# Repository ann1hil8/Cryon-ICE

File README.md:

# Cryon-ICE: High-Performance RISC-V Target Emulator & Hardware Debugger

Cryon-ICE is a high-speed real-time hardware debugger and target emulation platform built on the Microchip PolarFire SoC FPGA architecture. The system serves as an advanced bidirectional interface bridge designed to intercept, analyze, and process target system execution signals with sub-nanosecond timing precision. 

The architecture bridges a multi-core 64-bit Linux-capable RISC-V subsystem and flexible programmable fabric directly to an external emulation pod interface via high-density card edge connectors.

---

## Technical Architecture Overview

### 1. System Function & Target Application
* **Real-Time Emulation:** Provides deterministic, ultra-low-latency tracking and signal injection for vintage and modern processing buses.
* **Signal Intercept:** Actively hooks into address, data, and control structures of external hardware targets through dedicated, direction-controlled level shifters.
* **Bus Topologies:** Supports a universal expansion bus configuration, currently mapped to a physical PCIe card edge connector profile to interface directly with modular target emulation pods.

### 2. Primary Processing Core
The platform core utilizes the **Microchip PolarFire SoC FPGA** which integrates a hardened coherent CPU cluster alongside non-volatile programmable logic fabric.

* **Exact Part Number:** `MPFS025TC-FCVG484I` (Industrial Temperature Variant, 25K Logic Elements).
* **Microprocessor Sub-System (MSS):** * 1x RV64IMAC Monitor Core (E51 Performance Profile).
  * 4x RV64GC Application Cores (U54 Performance Profile, coherent execution cluster).
  * Hardened memory controllers supporting secure boot, asset protection, and full operating system execution (Linux).
* **Reference Baselines:** Hardware schematics and subsystem initialization fabrics are cross-referenced from the **BeagleV-Fire** open-hardware specification and the **MPFS-ICICLE-KIT** (PolarFire SoC Icicle Development Kit) base architectures.

### 3. Physical Mechanical Package
* **Package Designation:** `FCVG484` (Fine Pitch Flip-Chip Ball Grid Array).
* **Physical Package Envelope:** 19.0 mm x 19.0 mm square molded body package size.
* **Pin Matrix Array:** 484 physical active solder spheres mapped to a 22 x 22 structural matrix grid.
* **Ball Pitch ($P$):** 0.8 mm center-to-center pad spacing. This allows routing single escape tracks using conventional, cost-effective mechanical micro-drills rather than high-density interconnect (HDI) laser-vias.

### 4. PCB Design & Layout Constraints

#### Thermal and Decoupling Void
The physical layout strips away all copper landing pads within the center core of the 22 x 22 BGA matrix configuration, mirroring the physical depopulated ring profile of the `FCVG484` package silicon. This provides two critical routing advantages:
* **Decoupling Optimization:** Low-inductance 0.1 uF ceramic decoupling capacitors are placed directly on the bottom side of the PCB (Layer 4/6), directly beneath the processor power balls to suppress high-frequency transients.
* **Thermal Sink:** The internal center cavity is flooded with a continuous, unbroken Ground copper polygon pour on the outer layer, functioning as an integrated cooling block connected directly to internal system return layers.

#### Physical Layer Stackup Blueprint
The system requires a minimum of a 4-Layer or 6-Layer impedance-controlled configuration:
* **Layer 1 (Top/F.Cu):** Microstrip routing paths, BGA outer escape rings, high-speed transceiver runs, and level-shifter landing pads.
* **Layer 2 (Inner 1/In1.Cu):** Continuous, uninterrupted Ground ($GND$) reference plane. Provides immediate shield parameters for high-density breakout tracks.
* **Layer 3 (Inner 2/In2.Cu):** Split Power Plane ($V_{\text{DD}}$ Core Logic, $V_{\text{DDA}}$ Transceiver Supplies, and 3.3 V / 5.0 V I/O Peripheral Rails).
* **Layer 4 (Bottom/B.Cu):** Passives, decoupling capacitors under the BGA core cavity, and secondary escape routing structures.

---

## CAD Design Rules Matrix (KiCad Netclasses)

The board layout is constrained by specific routing rules configured within the project netclass matrix. Tracks are auto-routed and routed manually using single-ended configurations without generating layout violations.

| Net Class Name | Clearance | Track Width | Via Size | Via Drill | uVia Size | uVia Drill | DP Width | DP Gap |
| :--- | :--- | :--- | :--- | :--- | :--- | :--- | :--- | :--- |
| `BGA_Escape` | 0.127 mm | 0.127 mm | 0.400 mm | 0.200 mm | 0.400 mm | 0.200 mm | 0.127 mm | 0.150 mm |
| `Universal_Bus` | 0.150 mm | 0.200 mm | 0.600 mm | 0.300 mm | 0.600 mm | 0.300 mm | 0.200 mm | 0.200 mm |
| `Power_GND` | 0.200 mm | 0.500 mm | 0.800 mm | 0.400 mm | 0.800 mm | 0.400 mm | 0.600 mm | 0.250 mm |
| `Default` | 0.200 mm | 0.200 mm | 0.600 mm | 0.300 mm | 0.300 mm | 0.100 mm | 0.200 mm | 0.250 mm |

### Routing Mechanics
* **BGA Escape Plan:** Escape tracks (0.127 mm width) break out through the diagonal open channels between the BGA pads (0.400 mm pad diameter). Vias are placed inside the center void of each 4-pad diamond cluster to preserve spatial clearances.
* **Bus Expansion:** Upon exiting the physical boundary of the BGA footprint package, traces transition via the `Universal_Bus` netclass rules to 0.200 mm widths to improve trace reliability, signal propagation characteristics, and manufacturing yields over long runs.

---

## Future Roadmap Configurations

### I/O Channel Expansion
* **Target Scale:** Planned upgrade to scale the universal emulation bus up from 48 lines to **64 universal bidirectional I/O channels**.
* **Impact:** Requires mapping additional General Purpose I/O (GPIO) banks from the PolarFire fabric and scaling up the number of transceiver/buffer ICs.

### Alternate Pod Interconnect Profiles
* **Connector Variant Modularity:** Evaluation of replacing or augmenting the baseline standard PCIe card-edge footprint with multi-lane high-density, high-speed connector options (e.g., Amphenol PCIe M.2 Gen 3/Gen 4 card edge or specialized mezzanine interconnects) to decrease overall pod size profiles while protecting high-speed signal integrity.

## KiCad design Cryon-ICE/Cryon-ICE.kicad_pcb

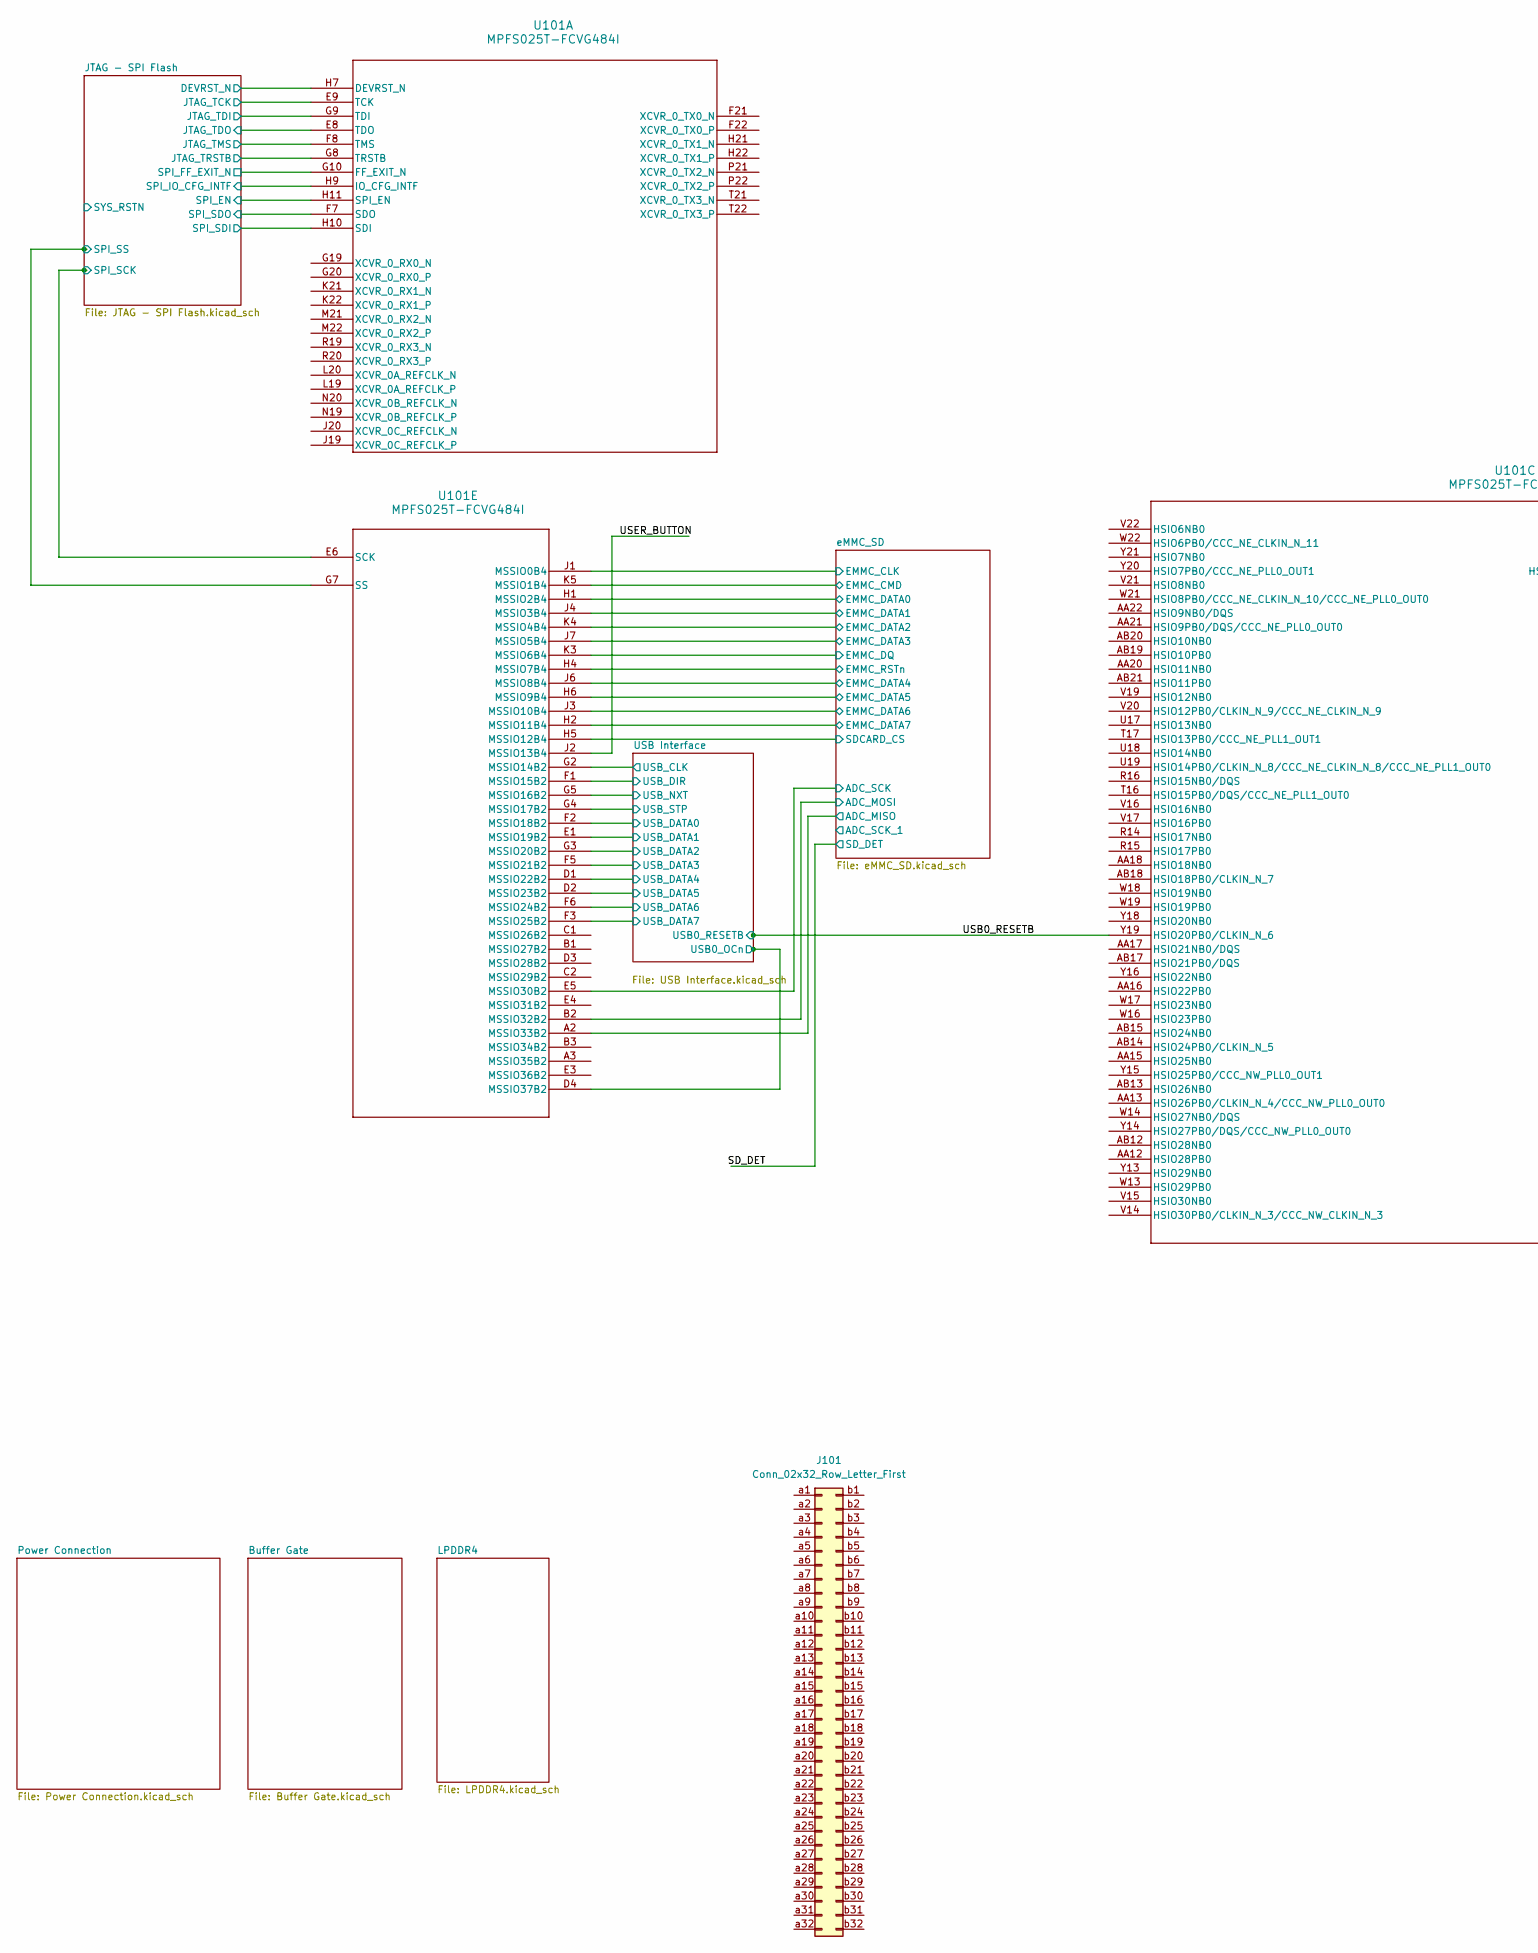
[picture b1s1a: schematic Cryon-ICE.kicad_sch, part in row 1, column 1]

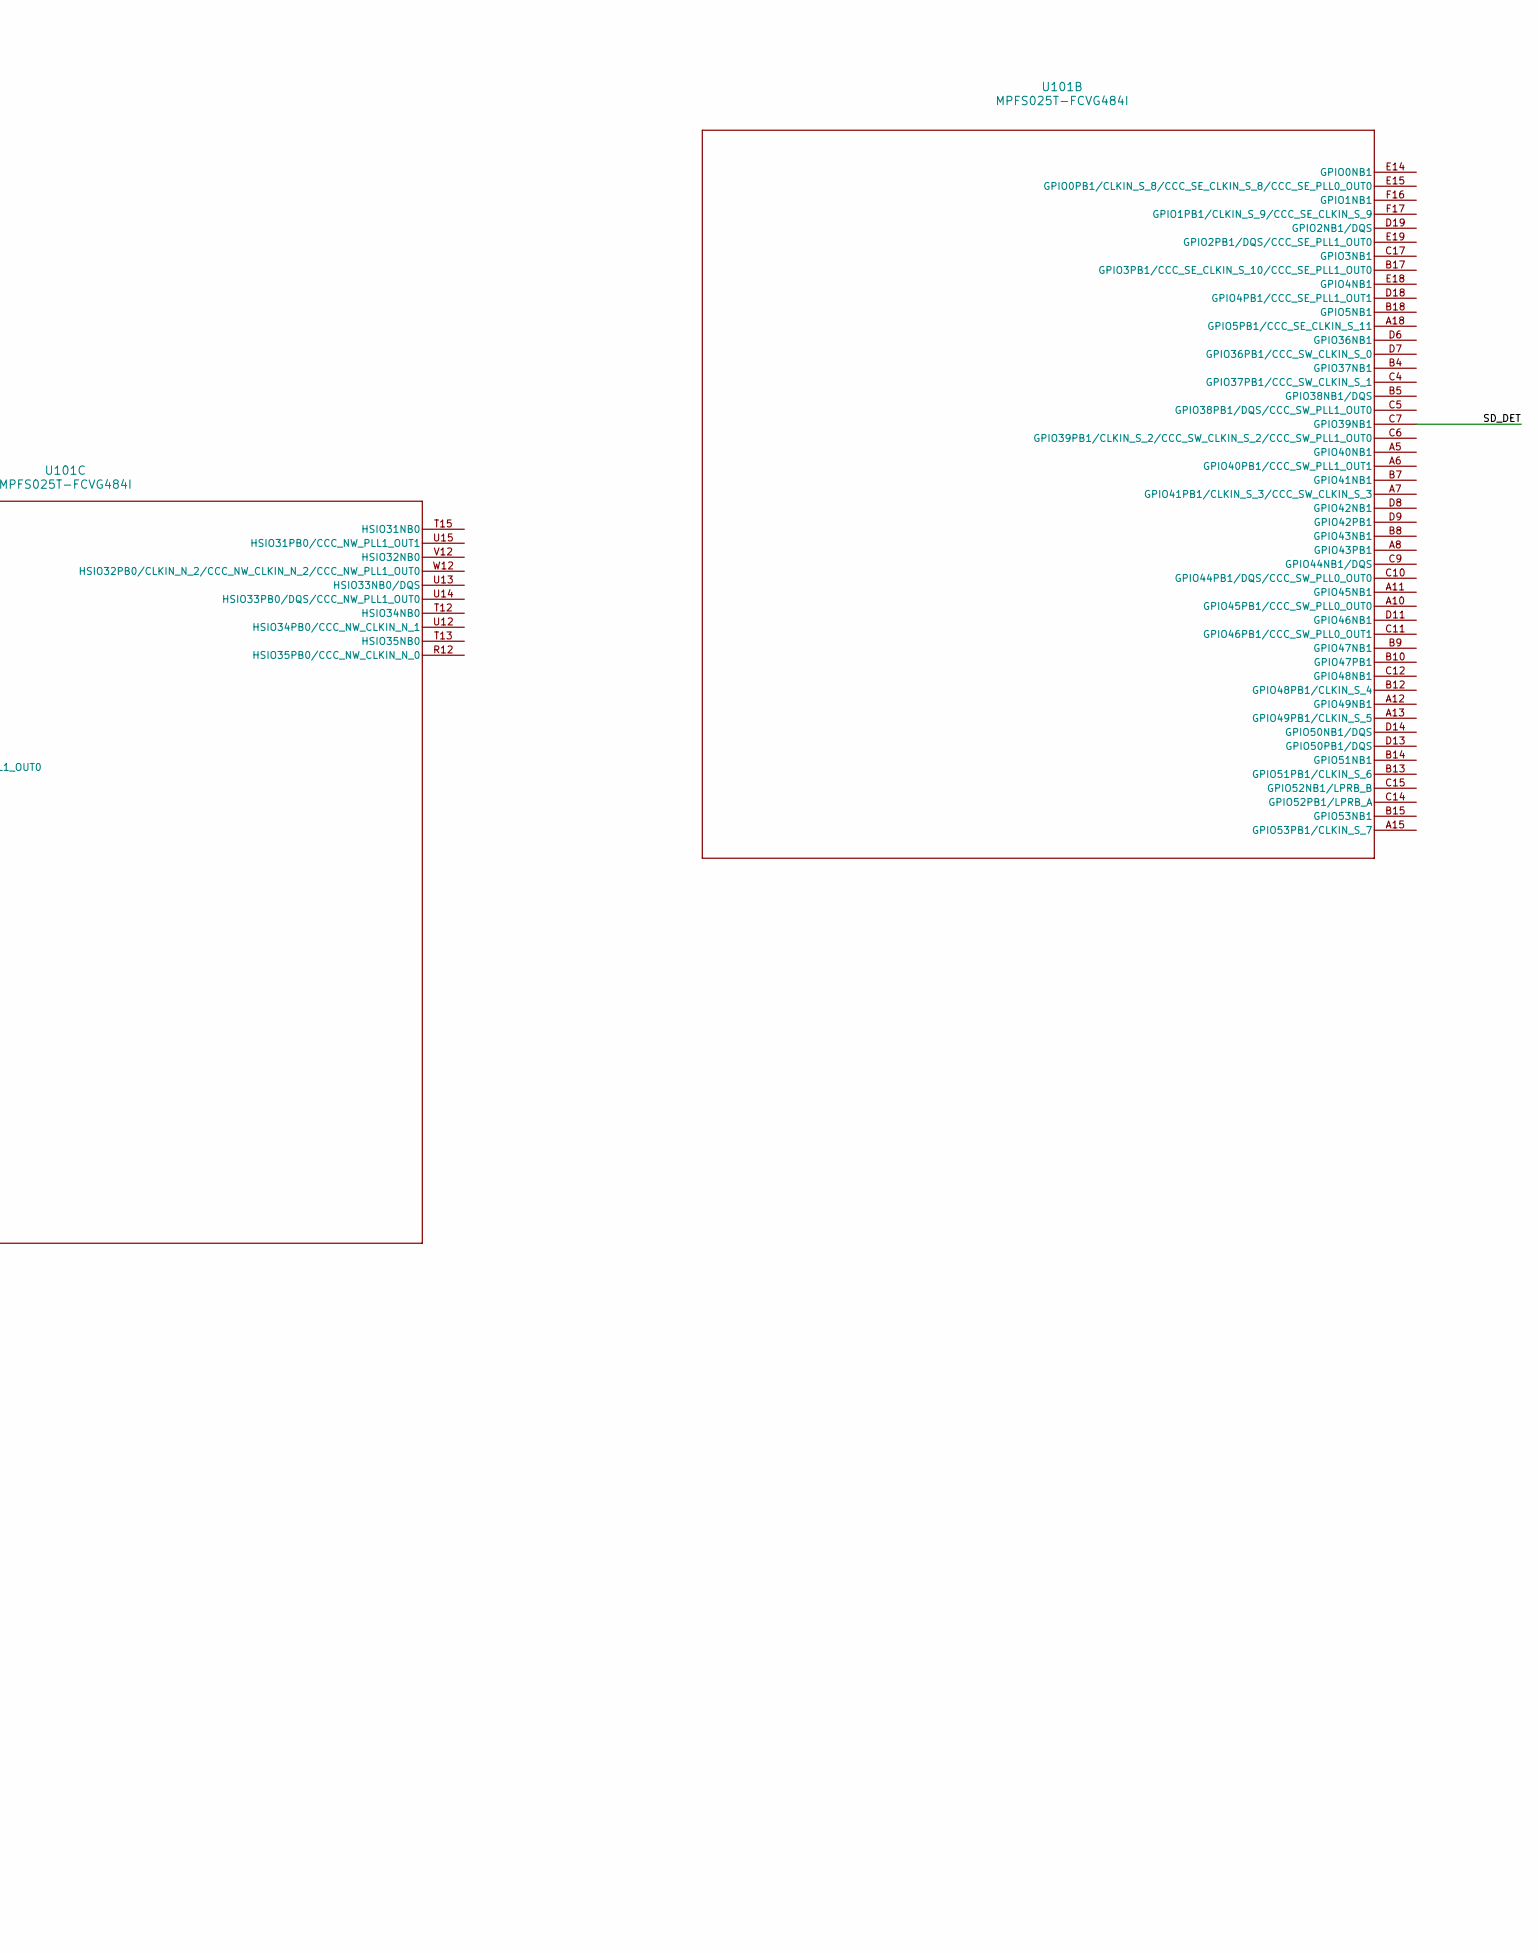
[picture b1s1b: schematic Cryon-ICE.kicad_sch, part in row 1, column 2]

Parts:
J101: Conn_02x32_Row_Letter_First; BUS_PCIexpress_x4
U101: MPFS025T-FCVG484I; MPFS250T&slash_MPFS160T&slash_MPFS095T&slash_MPFS025T-FCVG4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

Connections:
/JTAG - SPI Flash/DEVRST_N: U101.H7 (DEVRST_N); also elsewhere on the board
/JTAG - SPI Flash/JTAG_TDO: U101.E8 (TDO); also elsewhere on the board
/JTAG - SPI Flash/JTAT_TCK: U101.E9 (TCK); also elsewhere on the board
/JTAG - SPI Flash/JTAT_TDI: U101.G9 (TDI); also elsewhere on the board
/JTAG - SPI Flash/JTAT_TMS: U101.F8 (TMS); also elsewhere on the board
/JTAG - SPI Flash/JTAT_TRSTB: U101.G8 (TRSTB); also elsewhere on the board
/JTAG - SPI Flash/SPI_EN: U101.H11 (SPI_EN); also elsewhere on the board
/JTAG - SPI Flash/SPI_FF_EXIT_N: U101.G10 (FF_EXIT_N); also elsewhere on the board
/JTAG - SPI Flash/SPI_MISO: U101.H10 (SDI); also elsewhere on the board
/JTAG - SPI Flash/SPI_MODE: U101.H9 (IO_CFG_INTF); also elsewhere on the board
/JTAG - SPI Flash/SPI_SCK: U101.E6 (SCK); also elsewhere on the board
/JTAG - SPI Flash/SPI_SDO: U101.F7 (SDO); also elsewhere on the board
/JTAG - SPI Flash/SPI_SS: U101.G7 (SS); also elsewhere on the board
/SD_DET: U101.C7 (GPIO39NB1); also elsewhere on the board
/USB0_RESETB: U101.Y19 (HSIO20PB0/CLKIN_N_6); also elsewhere on the board
/USB Interface/USB0_OCn: U101.D4 (MSSIO37B2); also elsewhere on the board
/USB Interface/USB_CLK: U101.G2 (MSSIO14B2); also elsewhere on the board
/USB Interface/USB_DATA0: U101.F2 (MSSIO18B2); also elsewhere on the board
/USB Interface/USB_DATA1: U101.E1 (MSSIO19B2); also elsewhere on the board
/USB Interface/USB_DATA2: U101.G3 (MSSIO20B2); also elsewhere on the board
/USB Interface/USB_DATA3: U101.F5 (MSSIO21B2); also elsewhere on the board
/USB Interface/USB_DATA4: U101.D1 (MSSIO22B2); also elsewhere on the board
/USB Interface/USB_DATA5: U101.D2 (MSSIO23B2); also elsewhere on the board
/USB Interface/USB_DATA6: U101.F6 (MSSIO24B2); also elsewhere on the board
/USB Interface/USB_DATA7: U101.F3 (MSSIO25B2); also elsewhere on the board
/USB Interface/USB_DIR: U101.F1 (MSSIO15B2); also elsewhere on the board
/USB Interface/USB_NXT: U101.G5 (MSSIO16B2); also elsewhere on the board
/USB Interface/USB_STP: U101.G4 (MSSIO17B2); also elsewhere on the board
/USER_BUTTON: U101.J2 (MSSIO13B4)
/eMMC_SD/ADC_MISO: U101.A2 (MSSIO33B2); also elsewhere on the board
/eMMC_SD/ADC_MOSI: U101.B2 (MSSIO32B2); also elsewhere on the board
/eMMC_SD/ADC_SCK: U101.E5 (MSSIO30B2); also elsewhere on the board
/eMMC_SD/EMMC_CLK: U101.J1 (MSSIO0B4); also elsewhere on the board
/eMMC_SD/EMMC_CMD: U101.K5 (MSSIO1B4); also elsewhere on the board
/eMMC_SD/EMMC_DATA0: U101.H1 (MSSIO2B4); also elsewhere on the board
/eMMC_SD/EMMC_DATA1: U101.J4 (MSSIO3B4); also elsewhere on the board
/eMMC_SD/EMMC_DATA2: U101.K4 (MSSIO4B4); also elsewhere on the board
/eMMC_SD/EMMC_DATA3: U101.J7 (MSSIO5B4); also elsewhere on the board
/eMMC_SD/EMMC_DATA4: U101.J6 (MSSIO8B4); also elsewhere on the board
/eMMC_SD/EMMC_DATA5: U101.H6 (MSSIO9B4); also elsewhere on the board
/eMMC_SD/EMMC_DATA6: U101.J3 (MSSIO10B4); also elsewhere on the board
/eMMC_SD/EMMC_DATA7: U101.H2 (MSSIO11B4); also elsewhere on the board
/eMMC_SD/EMMC_DQ: U101.K3 (MSSIO6B4); also elsewhere on the board
/eMMC_SD/EMMC_RSTn: U101.H4 (MSSIO7B4); also elsewhere on the board
/eMMC_SD/SDCARD_CS: U101.H5 (MSSIO12B4); also elsewhere on the board

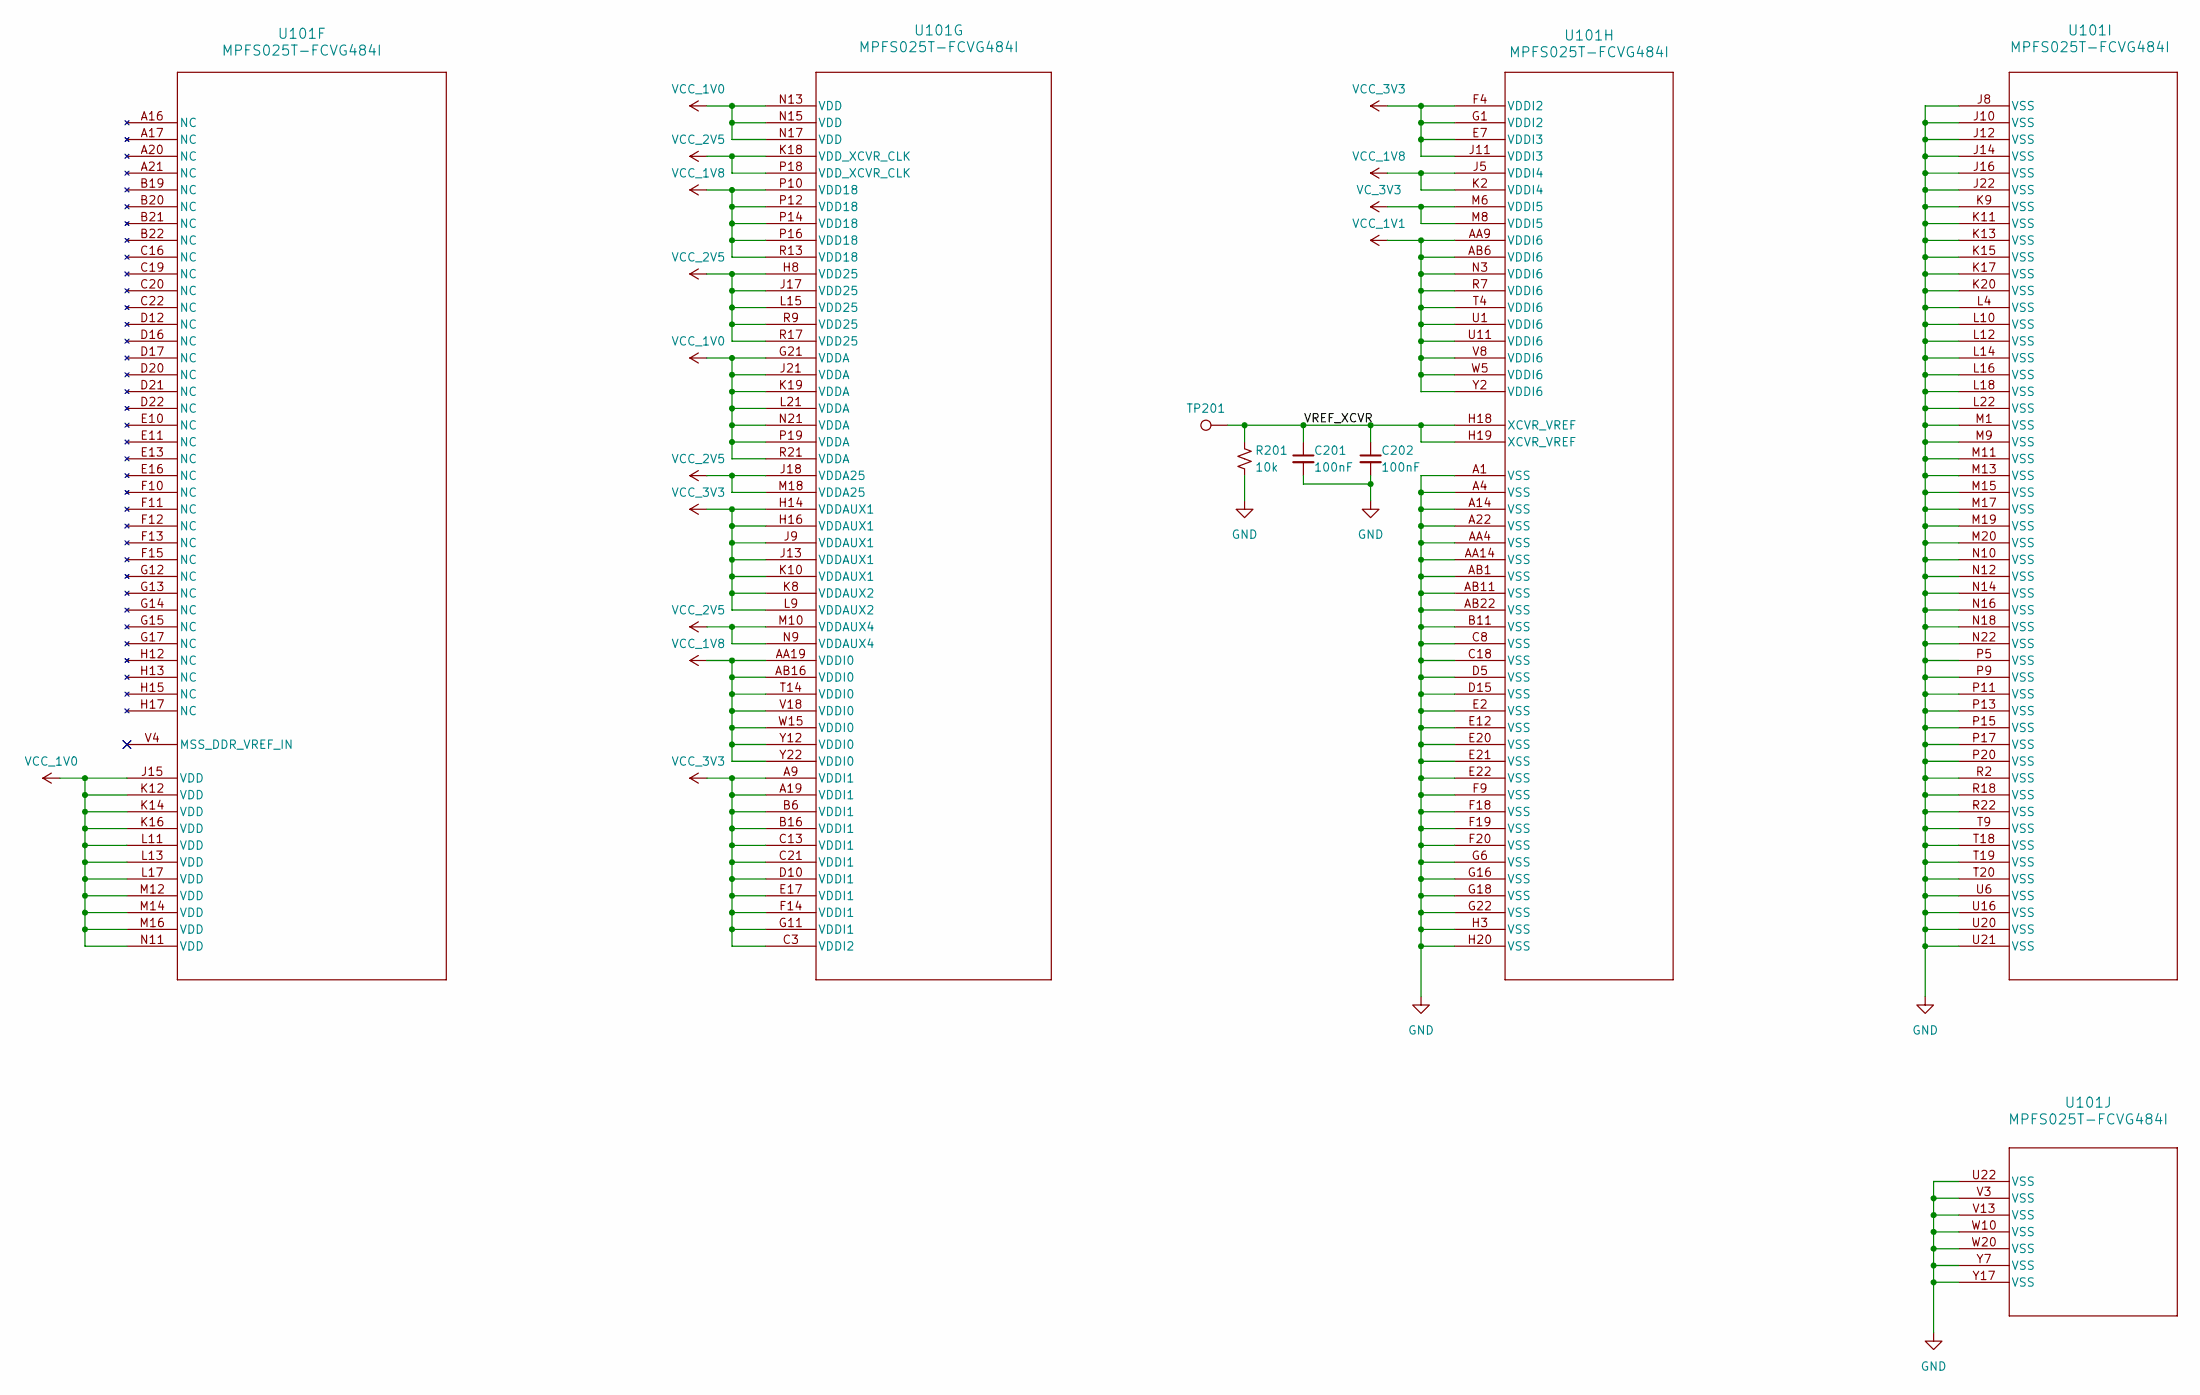
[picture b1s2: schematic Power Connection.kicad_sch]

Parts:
C201, C202: 100nF; C_0201_0603Metric
R201: 10k; R_0402_1005Metric
TP201: TestPoint; TestPoint_Pad_D1.0mm
U101: MPFS025T-FCVG484I; MPFS250T&slash_MPFS160T&slash_MPFS095T&slash_MPFS025T-FCVG4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

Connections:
/Power Connection/VREF_XCVR: C201.1, C202.1, R201.1, TP201.1 (1_1), U101.H18 (XCVR_VREF), U101.H19 (XCVR_VREF)
GND: C201.2, C202.2, R201.2, U101.A1 (VSS), U101.A4 (VSS), U101.A14 (VSS), U101.A22 (VSS), U101.AA4 (VSS), U101.AA14 (VSS), U101.AB1 (VSS), U101.AB11 (VSS), U101.AB22 (VSS), U101.B11 (VSS), U101.C8 (VSS), U101.C18 (VSS), U101.D5 (VSS), U101.D15 (VSS), U101.E2 (VSS), U101.E12 (VSS), U101.E20 (VSS), U101.E21 (VSS), U101.E22 (VSS), U101.F9 (VSS), U101.F18 (VSS), U101.F19 (VSS), U101.F20 (VSS), U101.G6 (VSS), U101.G16 (VSS), U101.G18 (VSS), U101.G22 (VSS), U101.H3 (VSS), U101.H20 (VSS), U101.J8 (VSS), U101.J10 (VSS), U101.J12 (VSS), U101.J14 (VSS), U101.J16 (VSS), U101.J22 (VSS), U101.K9 (VSS), U101.K11 (VSS), U101.K13 (VSS), U101.K15 (VSS), U101.K17 (VSS), U101.K20 (VSS), U101.L4 (VSS), U101.L10 (VSS), U101.L12 (VSS), U101.L14 (VSS), U101.L16 (VSS), U101.L18 (VSS), U101.L22 (VSS), U101.M1 (VSS), U101.M9 (VSS), U101.M11 (VSS), U101.M13 (VSS), U101.M15 (VSS), U101.M17 (VSS), U101.M19 (VSS), U101.M20 (VSS), U101.N10 (VSS), U101.N12 (VSS), U101.N14 (VSS), U101.N16 (VSS), U101.N18 (VSS), U101.N22 (VSS), U101.P5 (VSS), U101.P9 (VSS), U101.P11 (VSS), U101.P13 (VSS), U101.P15 (VSS), U101.P17 (VSS), U101.P20 (VSS), U101.R2 (VSS), U101.R18 (VSS), U101.R22 (VSS), U101.T9 (VSS), U101.T18 (VSS), U101.T19 (VSS), U101.T20 (VSS), U101.U6 (VSS), U101.U16 (VSS), U101.U20 (VSS), U101.U21 (VSS), U101.U22 (VSS), U101.V3 (VSS), U101.V13 (VSS), U101.W10 (VSS), U101.W20 (VSS), U101.Y7 (VSS), U101.Y17 (VSS); also elsewhere on the board
VCC_1V0: U101.G21 (VDDA), U101.J15 (VDD), U101.J21 (VDDA), U101.K12 (VDD), U101.K14 (VDD), U101.K16 (VDD), U101.K19 (VDDA), U101.L11 (VDD), U101.L13 (VDD), U101.L17 (VDD), U101.L21 (VDDA), U101.M12 (VDD), U101.M14 (VDD), U101.M16 (VDD), U101.N11 (VDD), U101.N13 (VDD), U101.N15 (VDD), U101.N17 (VDD), U101.N21 (VDDA), U101.P19 (VDDA), U101.R21 (VDDA)
VCC_1V1: U101.AA9 (VDDI6), U101.AB6 (VDDI6), U101.N3 (VDDI6), U101.R7 (VDDI6), U101.T4 (VDDI6), U101.U1 (VDDI6), U101.U11 (VDDI6), U101.V8 (VDDI6), U101.W5 (VDDI6), U101.Y2 (VDDI6); also elsewhere on the board
VCC_1V8: U101.AA19 (VDDI0), U101.AB16 (VDDI0), U101.J5 (VDDI4), U101.K2 (VDDI4), U101.P10 (VDD18), U101.P12 (VDD18), U101.P14 (VDD18), U101.P16 (VDD18), U101.R13 (VDD18), U101.T14 (VDDI0), U101.V18 (VDDI0), U101.W15 (VDDI0), U101.Y12 (VDDI0), U101.Y22 (VDDI0); also elsewhere on the board
VCC_2V5: U101.H8 (VDD25), U101.J17 (VDD25), U101.J18 (VDDA25), U101.K18 (VDD_XCVR_CLK), U101.L15 (VDD25), U101.M10 (VDDAUX4), U101.M18 (VDDA25), U101.N9 (VDDAUX4), U101.P18 (VDD_XCVR_CLK), U101.R9 (VDD25), U101.R17 (VDD25)
VCC_3V3: U101.A9 (VDDI1), U101.A19 (VDDI1), U101.B6 (VDDI1), U101.B16 (VDDI1), U101.C3 (VDDI2), U101.C13 (VDDI1), U101.C21 (VDDI1), U101.D10 (VDDI1), U101.E7 (VDDI3), U101.E17 (VDDI1), U101.F4 (VDDI2), U101.F14 (VDDI1), U101.G1 (VDDI2), U101.G11 (VDDI1), U101.H14 (VDDAUX1), U101.H16 (VDDAUX1), U101.J9 (VDDAUX1), U101.J11 (VDDI3), U101.J13 (VDDAUX1), U101.K8 (VDDAUX2), U101.K10 (VDDAUX1), U101.L9 (VDDAUX2); also elsewhere on the board
VC_3V3: U101.M6 (VDDI5), U101.M8 (VDDI5)

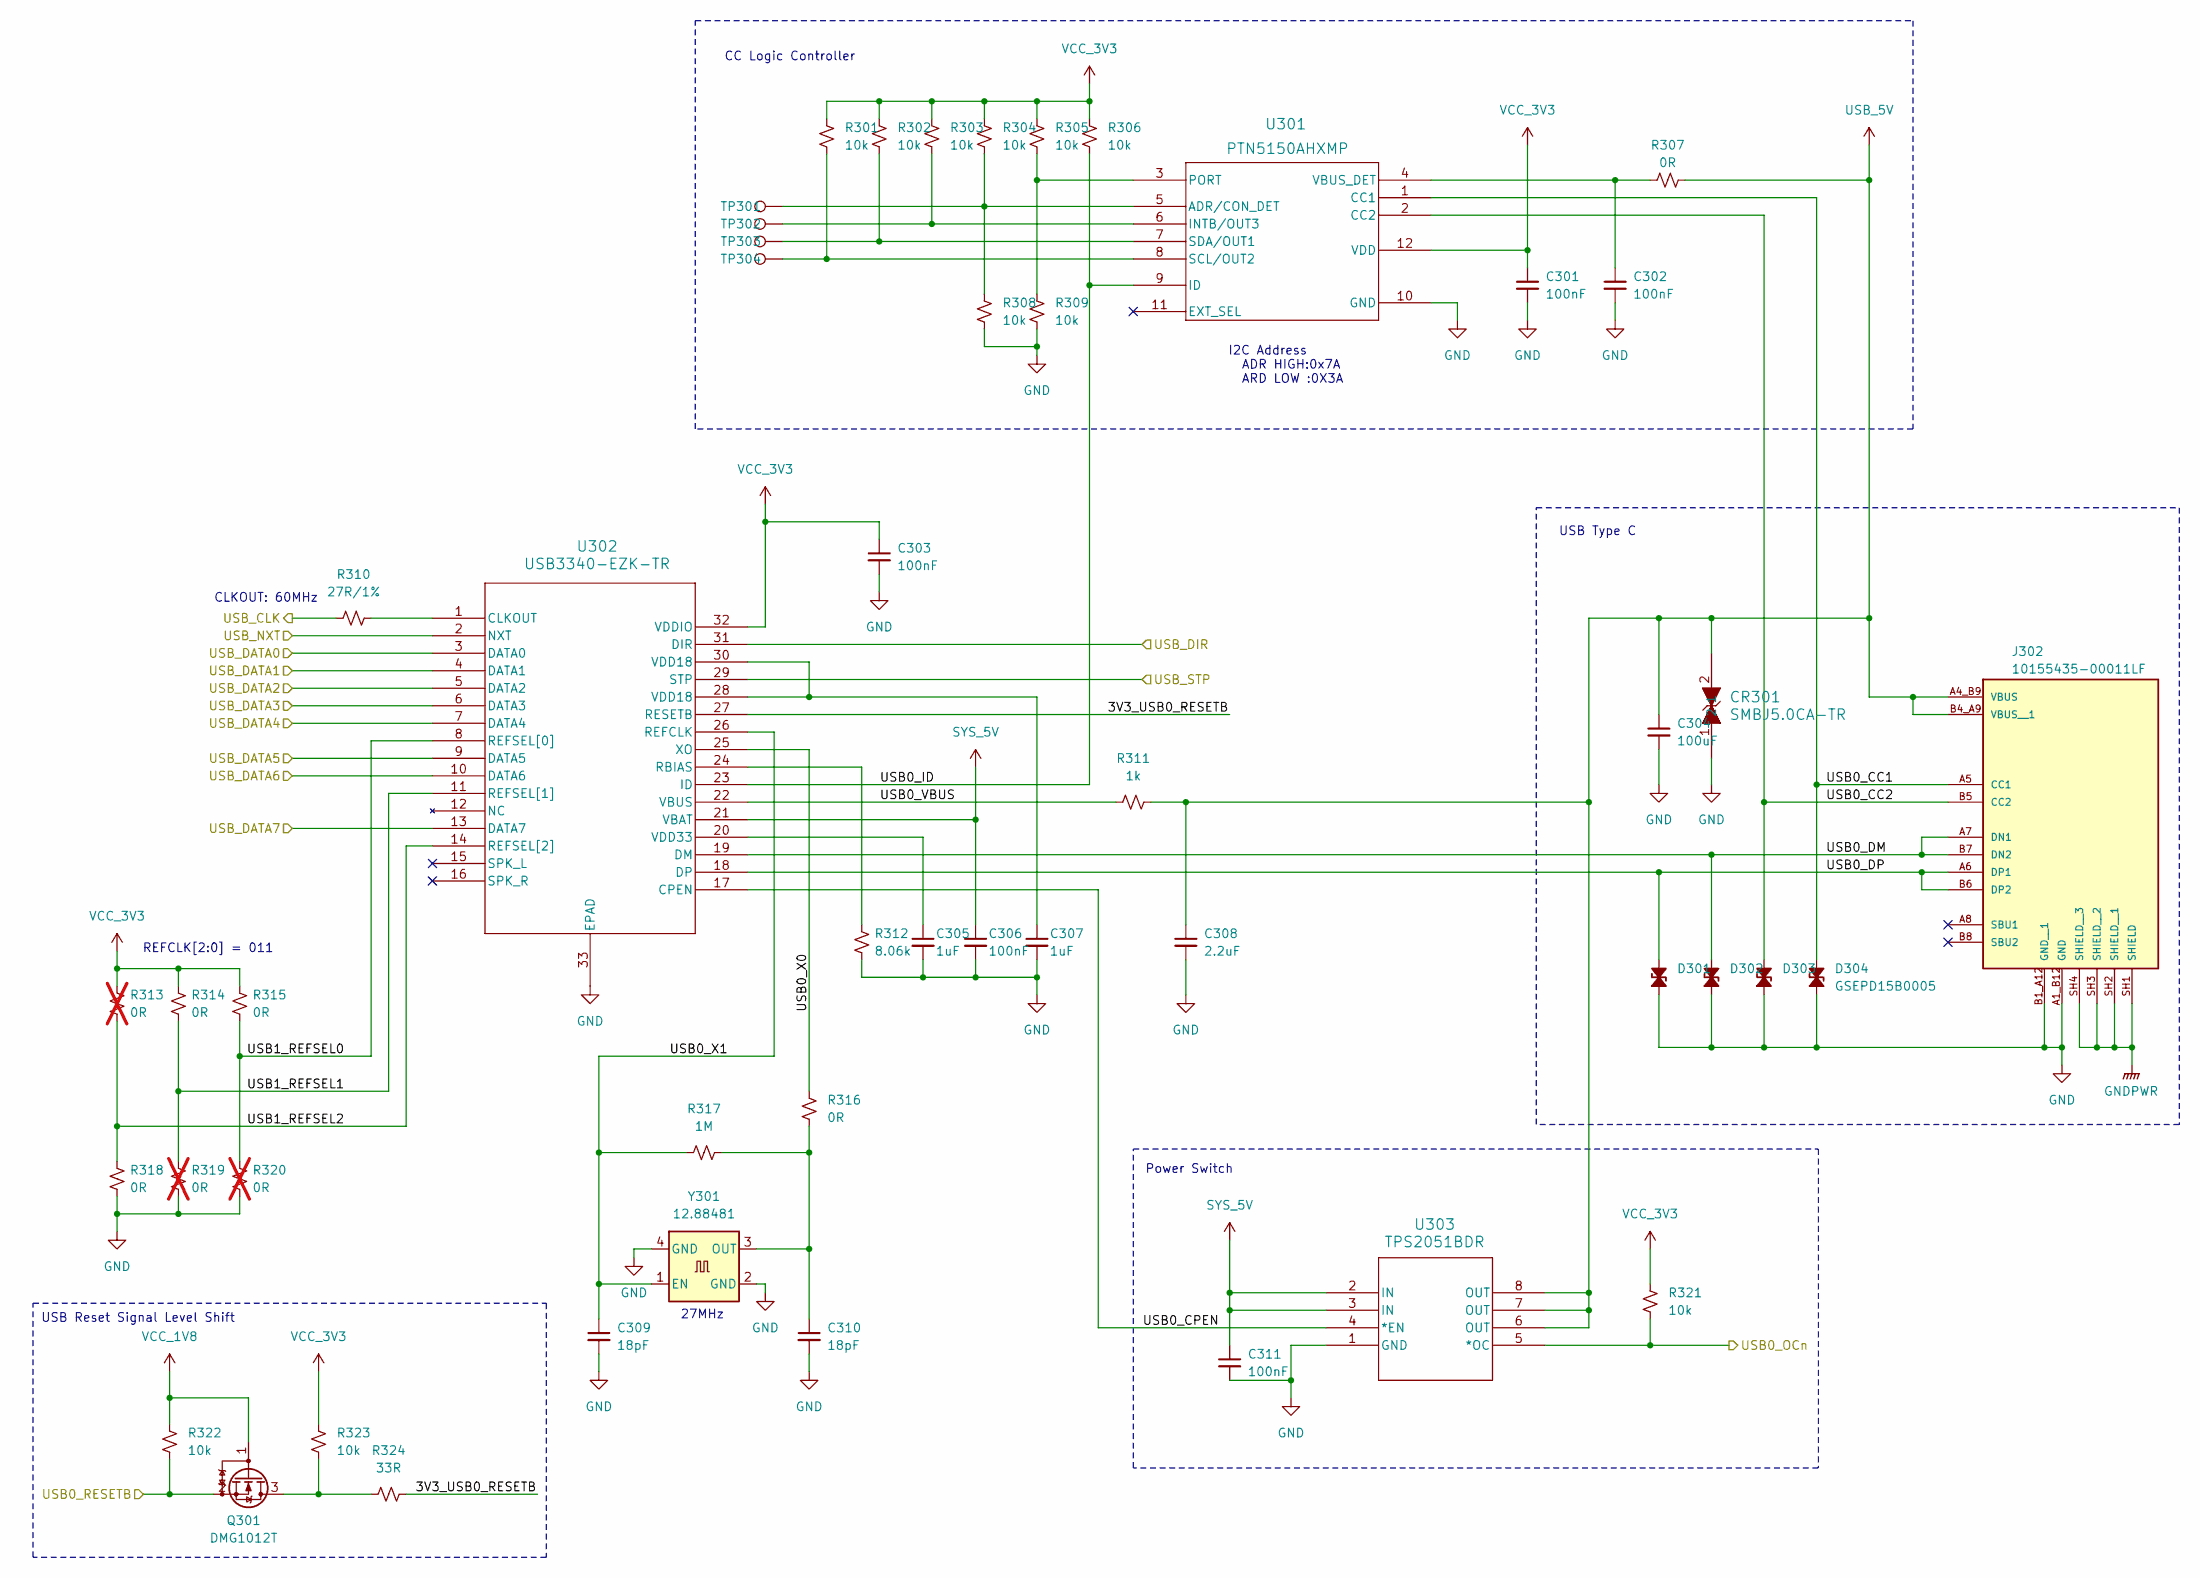
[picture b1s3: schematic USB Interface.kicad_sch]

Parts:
C301, C302, C303, C306, C311: 100nF; C_0402_1005Metric
C304: 100uF; C_0402_1005Metric
C305, C307: 1uF; C_0402_1005Metric
C308: 2.2uF; C_0603_1608Metric
C309, C310: 18pF; C_0402_1005Metric
CR301: SMBJ5.0CA-TR; SMB_STM
D301, D302, D303, D304: GSEPD15B0005; D_GSEPD15B0005_01005_0402Metric
J302: 10155435-00011LF; AMPHENOL_10155435-00011LF; PARTREV C
Q301: DMG1012T; DMG1012-SOT-523
R301, R302, R303, R304, R305, R306, R308, R309, R321, R322, R323: 10k; R_0402_1005Metric
R307, R314, R315, R316, R318: 0R; R_0402_1005Metric
R310: 27R/1%; R_0402_1005Metric
R311: 1k; R_0402_1005Metric
R312: 8.06k; R_0402_1005Metric
R313, R319, R320: 0R; R_0402_1005Metric; not fitted
R317: 1M; R_0402_1005Metric
R324: 33R; R_0402_1005Metric
TP301, TP302, TP303, TP304: TestPoint; TestPoint_Pad_D1.0mm
U301: PTN5150AHXMP; SOT1355-1_X2QFN12_NXP
U302: USB3340-EZK-TR; QFN32_5X5MC_MCH
U303: TPS2051BDR; D8
Y301: 12.88481; Oscillator_SMD_12.88481_EuroQuartz_XO32-4Pin_3.2x2.5mm

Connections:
/USB0_RESETB: Q301.2 (S), R322.2; also elsewhere on the board
/USB Interface/3V3_USB0_RESETB: R324.2, U302.27 (RESETB)
/USB Interface/USB0_CC1: D304.2 (A2), J302.A5 (CC1), U301.1 (CC1)
/USB Interface/USB0_CC2: D303.2 (A2), J302.B5 (CC2), U301.2 (CC2)
/USB Interface/USB0_CPEN: U302.17 (CPEN), U303.4 (*EN)
/USB Interface/USB0_DM: D302.2 (A2), J302.A7 (DN1), J302.B7 (DN2), U302.19 (DM)
/USB Interface/USB0_DP: D301.2 (A2), J302.A6 (DP1), J302.B6 (DP2), U302.18 (DP)
/USB Interface/USB0_ID: R306.2, U301.9 (ID), U302.23 (ID)
/USB Interface/USB0_OCn: R321.2, U303.5 (*OC); also elsewhere on the board
/USB Interface/USB0_VBUS: R311.1, U302.22 (VBUS)
/USB Interface/USB0_X0: R316.1, U302.25 (XO)
/USB Interface/USB0_X1: C309.1, R317.1, U302.26 (REFCLK), Y301.1 (EN)
/USB Interface/USB1_REFSEL0: R315.2, R320.1, U302.8 (REFSEL[0])
/USB Interface/USB1_REFSEL1: R314.2, R319.1, U302.11 (REFSEL[1])
/USB Interface/USB1_REFSEL2: R313.2, R318.1, U302.14 (REFSEL[2])
/USB Interface/USB_CLK: R310.1; also elsewhere on the board
/USB Interface/USB_DATA0: U302.3 (DATA0); also elsewhere on the board
/USB Interface/USB_DATA1: U302.4 (DATA1); also elsewhere on the board
/USB Interface/USB_DATA2: U302.5 (DATA2); also elsewhere on the board
/USB Interface/USB_DATA3: U302.6 (DATA3); also elsewhere on the board
/USB Interface/USB_DATA4: U302.7 (DATA4); also elsewhere on the board
/USB Interface/USB_DATA5: U302.9 (DATA5); also elsewhere on the board
/USB Interface/USB_DATA6: U302.10 (DATA6); also elsewhere on the board
/USB Interface/USB_DATA7: U302.13 (DATA7); also elsewhere on the board
/USB Interface/USB_DIR: U302.31 (DIR); also elsewhere on the board
/USB Interface/USB_NXT: U302.2 (NXT); also elsewhere on the board
/USB Interface/USB_STP: U302.29 (STP); also elsewhere on the board
GND: C301.2, C302.2, C303.2, C304.2, C305.2, C306.2, C307.2, C308.2, C309.2, C310.2, C311.2, CR301.1, D301.1 (A1), D302.1 (A1), D303.1 (A1), D304.1 (A1), J302.A1_B12 (GND), J302.B1_A12 (GND__1), R308.2, R309.2, R312.2, R318.2, R319.2, R320.2, U301.10 (GND), U302.33 (EPAD), U303.1 (GND), Y301.2 (GND), Y301.4 (GND); also elsewhere on the board
GNDPWR: J302.SH1 (SHIELD), J302.SH2 (SHIELD__1), J302.SH3 (SHIELD__2), J302.SH4 (SHIELD__3)
unnamed: C307.1, U302.28 (VDD18), U302.30 (VDD18)
unnamed: Q301.3 (D), R323.2, R324.1
unnamed: R304.2, R308.1, TP301.1 (1_1), U301.5 (ADR/CON_DET)
unnamed: R303.2, TP302.1 (1_1), U301.6 (INTB/OUT3)
unnamed: R305.2, R309.1, U301.3 (PORT)
unnamed: R301.2, TP304.1 (1_1), U301.8 (SCL/OUT2)
unnamed: R302.2, TP303.1 (1_1), U301.7 (SDA/OUT1)
unnamed: C302.1, R307.1, U301.4 (VBUS_DET)
unnamed: R310.2, U302.1 (CLKOUT)
unnamed: R312.1, U302.24 (RBIAS)
unnamed: C305.1, U302.20 (VDD33)
unnamed: C310.1, R316.2, R317.2, Y301.3 (OUT)
SYS_5V: C306.1, C311.1, U302.21 (VBAT), U303.2 (IN), U303.3 (IN)
USB_5V: C304.1, C308.1, CR301.2, J302.A4_B9 (VBUS), J302.B4_A9 (VBUS__1), R307.2, R311.2, U303.6 (OUT), U303.7 (OUT), U303.8 (OUT)
VCC_1V8: Q301.1 (G), R322.1; also elsewhere on the board
VCC_3V3: C301.1, C303.1, R301.1, R302.1, R303.1, R304.1, R305.1, R306.1, R313.1, R314.1, R315.1, R321.1, R323.1, U301.12 (VDD), U302.32 (VDDIO); also elsewhere on the board

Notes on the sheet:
USB Reset Signal Level Shift
CC Logic Controller
REFCLK[2:0] = 011
27MHz
USB Type C
CLKOUT: 60MHz
I2C Address ADR HIGH:0x7A ARD LOW :0X3A
Power Switch
